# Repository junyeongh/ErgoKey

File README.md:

# ErgoKey

ErgoKey is $7 \times 4$ column-staggered split keyboard heavily inspired by the [Timception/Drift](https://github.com/Timception/Drift) and [kata0510/Lily58](https://github.com/kata0510/Lily58).

## Layout

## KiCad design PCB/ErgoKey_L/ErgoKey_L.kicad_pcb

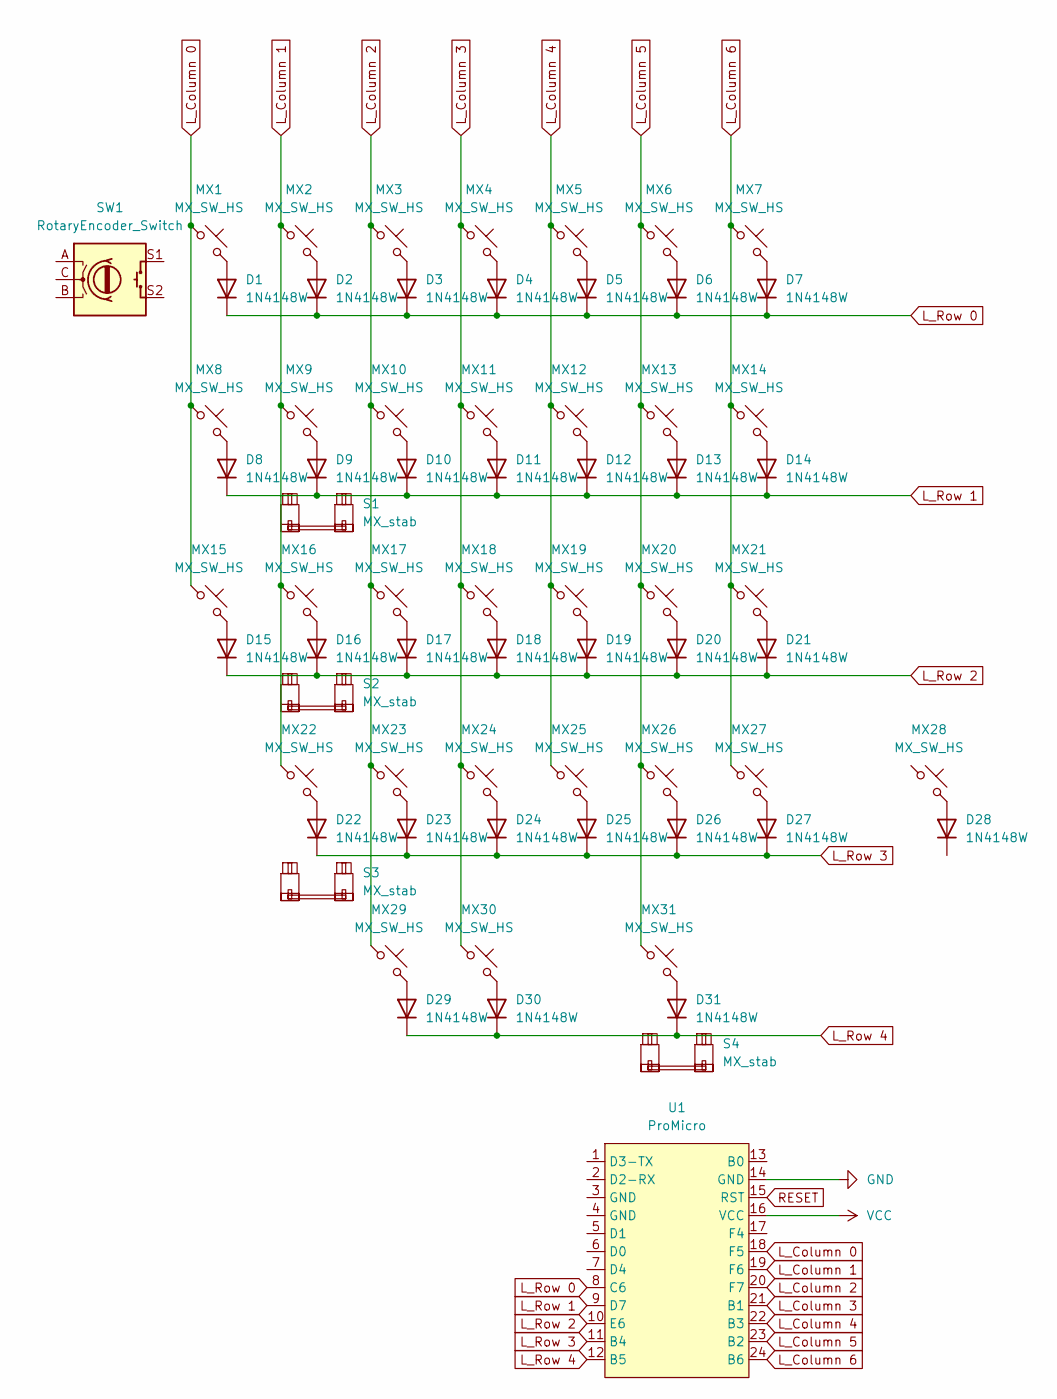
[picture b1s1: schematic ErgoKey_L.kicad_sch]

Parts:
D1, D2, D3, D4, D5, D6, D7, D8, D9, D10, D11, D12, D13, D14, D15, D16, D17, D18, D19, D20, D21, D22, D23, D24, D25, D26, D27, D28, D29, D30, D31: 1N4148W; D_SOD-123
MX1, MX2, MX3, MX4, MX5, MX6, MX7, MX8, MX9, MX10, MX11, MX12, MX13, MX14, MX15, MX16, MX17, MX18, MX19, MX20, MX21, MX22, MX23, MX24, MX25, MX26, MX27, MX28, MX29, MX30, MX31: MX_SW_HS; SW_MX_HS_CPG151101S11_1u
S1, S2, S3, S4: MX_stab; STAB_MX_2u
SW1: RotaryEncoder_Switch; RotaryEncoder_Alps_EC11E-Switch_Vertical_H20mm
U1: ProMicro; ProMicro_USBup

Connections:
L_Column 0: MX1.1, MX8.1, MX15.1, U1.18 (F5)
L_Column 1: MX2.1, MX9.1, MX16.1, MX22.1, U1.19 (F6)
L_Column 2: MX3.1, MX10.1, MX17.1, MX23.1, MX29.1, U1.20 (F7)
L_Column 3: MX4.1, MX11.1, MX18.1, MX24.1, MX30.1, U1.21 (B1)
L_Column 4: MX5.1, MX12.1, MX19.1, MX25.1, U1.22 (B3)
L_Column 5: MX6.1, MX13.1, MX20.1, MX26.1, MX31.1, U1.23 (B2)
L_Column 6: MX7.1, MX14.1, MX21.1, MX27.1, U1.24 (B6)
L_Row 0: D1.1 (K), D2.1 (K), D3.1 (K), D4.1 (K), D5.1 (K), D6.1 (K), D7.1 (K), U1.8 (C6)
L_Row 1: D8.1 (K), D9.1 (K), D10.1 (K), D11.1 (K), D12.1 (K), D13.1 (K), D14.1 (K), U1.9 (D7)
L_Row 2: D15.1 (K), D16.1 (K), D17.1 (K), D18.1 (K), D19.1 (K), D20.1 (K), D21.1 (K), U1.10 (E6)
L_Row 3: D22.1 (K), D23.1 (K), D24.1 (K), D25.1 (K), D26.1 (K), D27.1 (K), U1.11 (B4)
L_Row 4: D29.1 (K), D30.1 (K), D31.1 (K), U1.12 (B5)
unnamed: D1.2 (A), MX1.2
unnamed: D2.2 (A), MX2.2
unnamed: D3.2 (A), MX3.2
unnamed: D4.2 (A), MX4.2
unnamed: D5.2 (A), MX5.2
unnamed: D6.2 (A), MX6.2
unnamed: D7.2 (A), MX7.2
unnamed: D8.2 (A), MX8.2
unnamed: D9.2 (A), MX9.2
unnamed: D10.2 (A), MX10.2
unnamed: D11.2 (A), MX11.2
unnamed: D12.2 (A), MX12.2
unnamed: D13.2 (A), MX13.2
unnamed: D14.2 (A), MX14.2
unnamed: D15.2 (A), MX15.2
unnamed: D16.2 (A), MX16.2
unnamed: D17.2 (A), MX17.2
unnamed: D18.2 (A), MX18.2
unnamed: D19.2 (A), MX19.2
unnamed: D20.2 (A), MX20.2
unnamed: D21.2 (A), MX21.2
unnamed: D22.2 (A), MX22.2
unnamed: D23.2 (A), MX23.2
unnamed: D24.2 (A), MX24.2
unnamed: D25.2 (A), MX25.2
unnamed: D26.2 (A), MX26.2
unnamed: D27.2 (A), MX27.2
unnamed: D28.2 (A), MX28.2
unnamed: D29.2 (A), MX29.2
unnamed: D30.2 (A), MX30.2
unnamed: D31.2 (A), MX31.2

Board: 2 copper layers, 68 parts (62 on the bottom side), 43 nets, no tracks yet.

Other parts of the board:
U2: nice_nano; nice_nano_AH_USBup

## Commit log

2024-07-25 one small step
2024-07-26 worked on the right-hand side and changed dev board to nice!nano
